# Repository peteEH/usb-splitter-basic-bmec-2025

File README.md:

# usb-splitter-basic-bmec-2025

Basic Type-A split out to data and power only USB connectors

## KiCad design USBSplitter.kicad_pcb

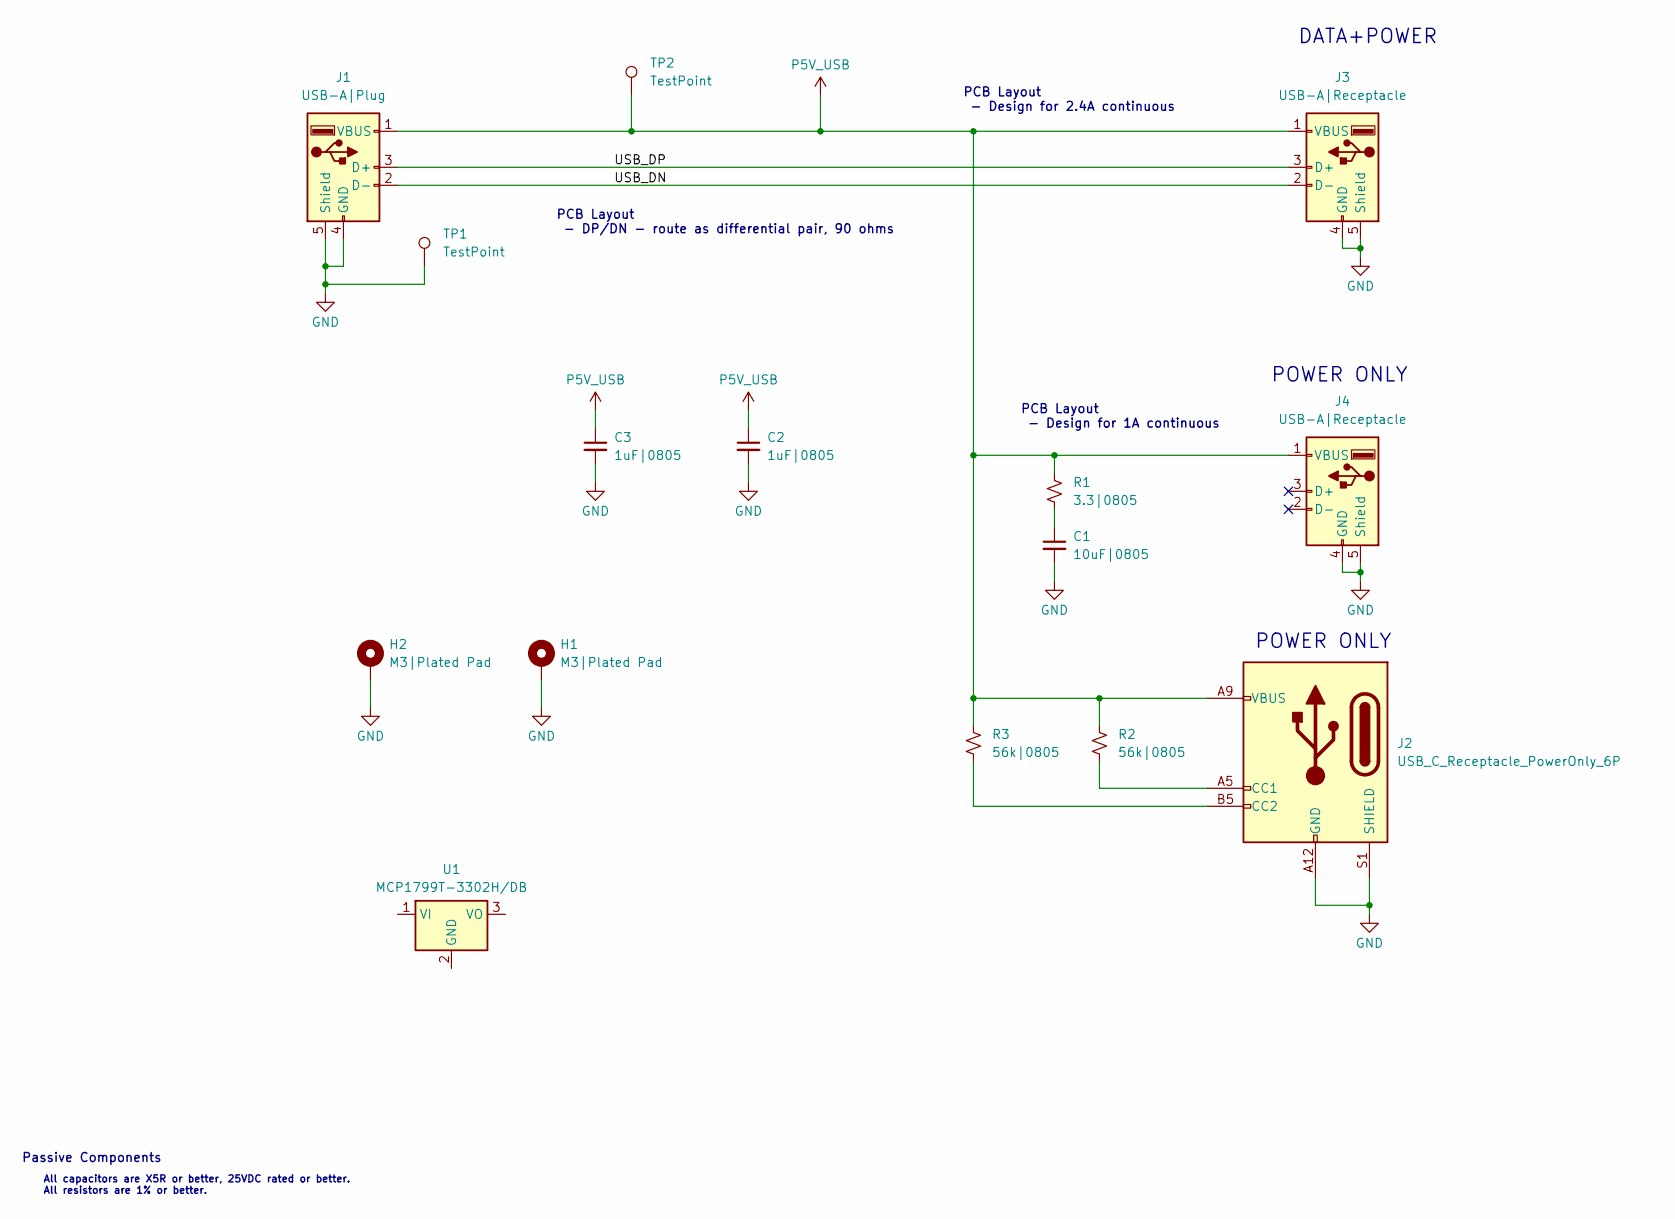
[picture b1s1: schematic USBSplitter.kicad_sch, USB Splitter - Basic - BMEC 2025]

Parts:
C1: 10uF|0805; C_0805_2012Metric
C2, C3: 1uF|0805; C_0805_2012Metric
H1, H2: M3|Plated Pad; MountingHole_3.2mm_M3_DIN965_Pad
J1: USB-A|Plug; USB_A_CNCTech_1001-011-01101_Horizontal
J2: USB_C_Receptacle_PowerOnly_6P; USB_C_Receptacle_GCT_USB4125-xx-x_6P_TopMnt_Horizontal
J3, J4: USB-A|Receptacle; USB_A_Molex_67643_Horizontal
R1: 3.3|0805; R_0805_2012Metric
R2, R3: 56k|0805; R_0805_2012Metric
TP1, TP2: TestPoint; TestPoint_Loop_D1.80mm_Drill1.0mm_Beaded
U1: MCP1799T-3302H/DB

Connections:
/USB_DN: J1.2 (D-), J3.2 (D-)
/USB_DP: J1.3 (D+), J3.3 (D+)
GND: C1.2, C2.2, C3.2, H1.1, H2.1, J1.4 (GND), J1.5 (Shield), J2.A12 (GND), J2.B12 (GND), J2.S1 (SHIELD), J3.4 (GND), J3.5 (Shield), J4.4 (GND), J4.5 (Shield), TP1.1
unnamed: C1.1, R1.2
unnamed: J2.A5 (CC1), R2.2
unnamed: J2.B5 (CC2), R3.2
P5V_USB: C2.1, C3.1, J1.1 (VBUS), J2.A9 (VBUS), J2.B9 (VBUS), J3.1 (VBUS), J4.1 (VBUS), R1.1, R2.1, R3.1, TP2.1

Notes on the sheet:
All capacitors are X5R or better, 25VDC rated or better. All resistors are 1% or better.
PCB Layout - DP/DN - route as differential pair, 90 ohms
Passive Components
PCB Layout - Design for 2.4A continuous
PCB Layout - Design for 1A continuous
POWER ONLY
DATA+POWER

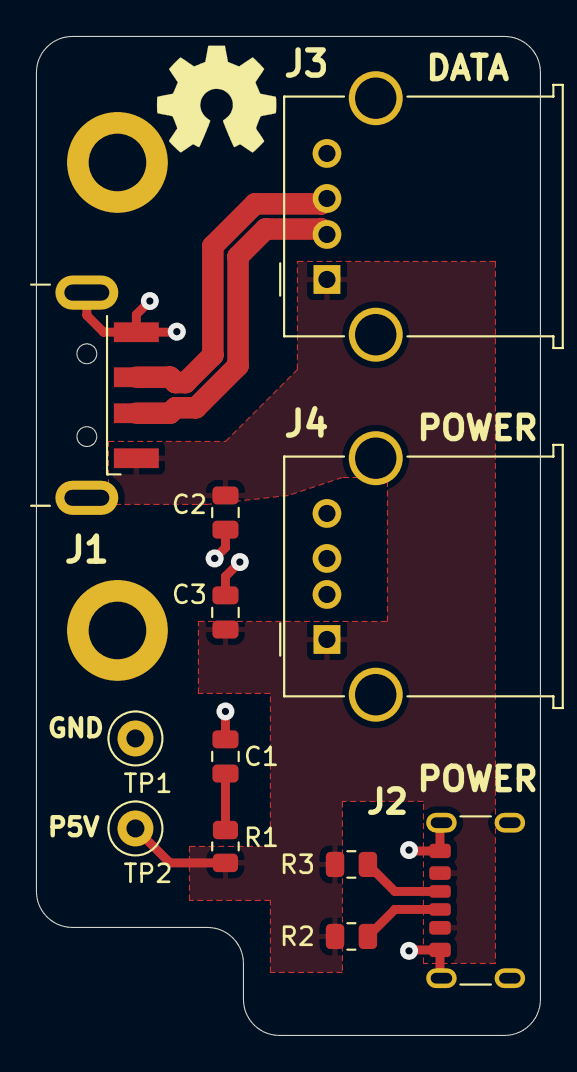
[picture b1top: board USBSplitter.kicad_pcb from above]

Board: 2 copper layers, 28.0 x 55.5 mm, 14 parts (0 on the bottom side), 7 nets.

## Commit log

2025-09-27 Add project description to README
    Added a brief description of the project.
2025-09-27 initial design files - basic splitter
